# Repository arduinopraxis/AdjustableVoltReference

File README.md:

# AdjustableVoltReference
Adjustable Voltage Reference with LM741
see project details on Hackaday - https://hackaday.io/project/190557-adjustable-voltage-reference-with-opamp-741

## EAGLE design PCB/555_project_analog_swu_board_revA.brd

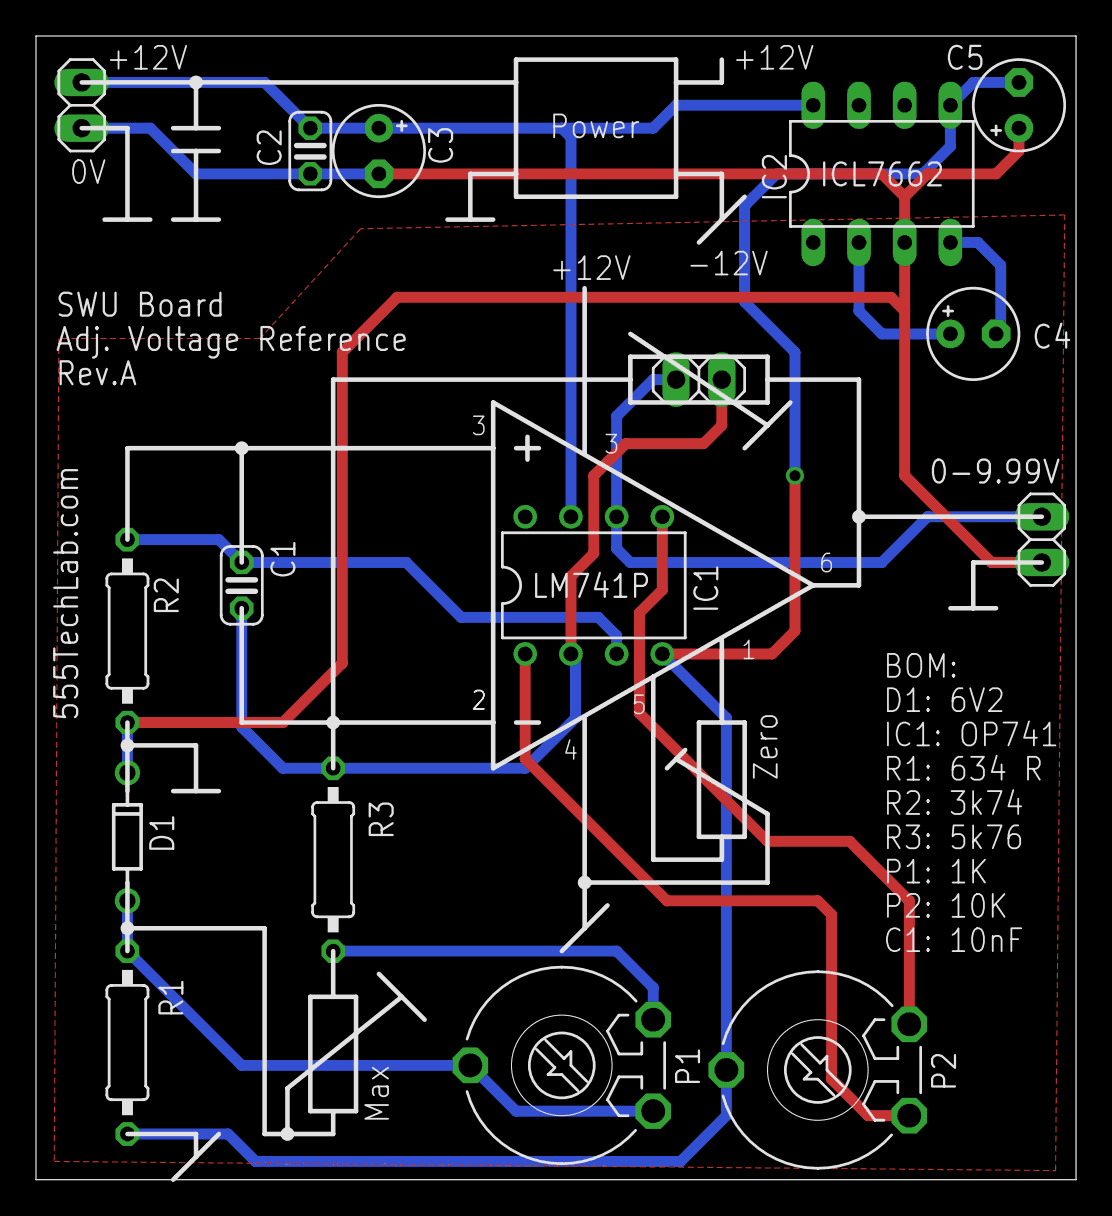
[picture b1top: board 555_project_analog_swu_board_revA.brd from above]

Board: 2 copper layers, 57.8 x 63.5 mm, 16 parts (0 on the bottom side), 12 nets.

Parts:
C1: C025-024X044
C2: 100nF; C025-024X044
C3, C4, C5: 10uF; E2,5-5
D1: DIODE-ZENERPTH; DIODE-ZENER
IC1: LM741P; DIL08
IC2: ICL7662; DIL08
K1: 1X02
K3: Codschalter; 1X02
K5: 0-9.99V; 1X02
P1: Max.; LI10
P2: Zero; LI10
R1, R2, R3: 0207/10

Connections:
0: IC1.6, K3.2, K5.1
+12V: C2.1, C3.+, IC1.7, IC2.8, K1.1
-12V: C5.-, IC1.4, IC2.5, P2.S, R1.2
C: C1.2, IC1.2, K3.1, R3.1
GND: C2.2, C3.-, C5.+, D1.P$1, IC2.3, K1.2, K5.2, R2.2
unnamed: IC1.1, P2.A
unnamed: IC1.5, P2.E
unnamed: C1.1, IC1.3, R2.1
unnamed: P1.E, R3.2
unnamed: D1.P$2, P1.A, P1.S, R1.1
unnamed: C4.+, IC2.2
unnamed: C4.-, IC2.4

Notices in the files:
parts and their libraries:
SparkFun-DiscreteSemi: Licensing: Creative Commons ShareAlike 4.0 International - https://creativecommons.org/licenses/by-sa/4.0
